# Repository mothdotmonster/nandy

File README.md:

# Nandy the NAND Gate

Nandy is a great friend who can help you make all kinds of decisions, as long as you decision has two digital inputs and one digital output.

Nandy is a breadboard-compatible NAND gate that you can hold in your hand. it's made as a teaching tool for electronics beginners to be able to learn how logic gates work with a simple and fun example of one.

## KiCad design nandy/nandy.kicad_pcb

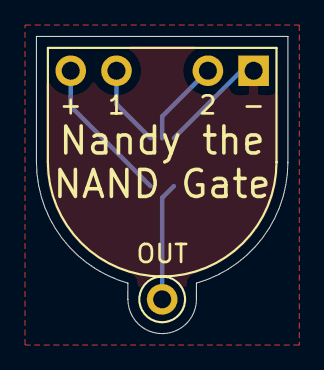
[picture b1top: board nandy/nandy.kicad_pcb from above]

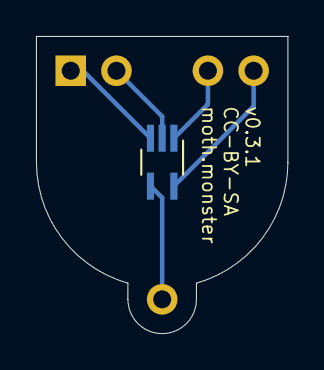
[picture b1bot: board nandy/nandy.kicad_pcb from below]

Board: 2 copper layers, 14.0 x 16.5 mm, 4 parts (4 on the bottom side), 5 nets.

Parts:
J1, J2: Conn_01x02_Male; PinHeader_1x02_P2.54mm_Vertical
J3: OUT; PinHeader_1x01_P2.54mm_Vertical
U1: 74LVC1G00; SOT-353_SC-70-5_Handsoldering

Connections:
/1: J1.1, U1.1
/2: J2.2, U1.2
/OUT: J3.1, U1.4
GND: J2.1, U1.3
VCC: J1.2, U1.5

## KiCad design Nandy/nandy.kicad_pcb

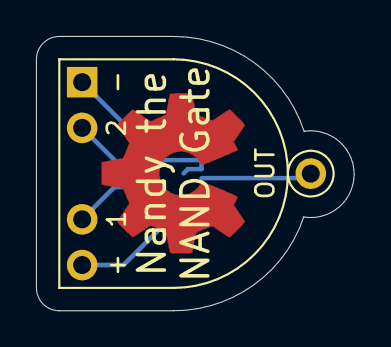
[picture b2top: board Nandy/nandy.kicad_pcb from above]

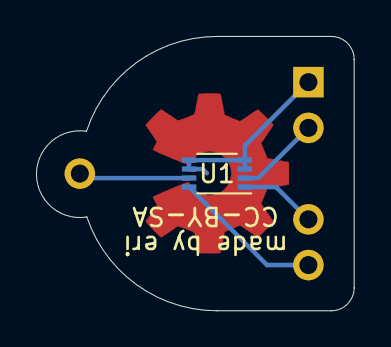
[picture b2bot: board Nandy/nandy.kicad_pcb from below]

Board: 2 copper layers, 17.7 x 15.2 mm, 4 parts (4 on the bottom side), 5 nets.

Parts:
J1, J2: Conn_01x02; PinHeader_1x02_P2.54mm_Vertical
J4: OUT; PinHeader_1x01_P2.54mm_Vertical
U1: 74LVC2G00; VSSOP-8_2.3x2mm_P0.5mm

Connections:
GND: J2.1, U1.3, U1.4, U1.5, U1.6
unnamed: J1.1, U1.1
unnamed: J2.2, U1.2
unnamed: J4.1, U1.7
VCC: J1.2, U1.8

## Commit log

2021-04-10 Add license
2021-04-10 Add gitignore
2021-04-10 Add the actual PCB
2021-04-10 Add first picture
2021-04-10 removing unessecary files
2021-04-16 add logo and website link
2021-04-28 total redesign

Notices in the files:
Nandy/nandy.kicad_pcb:
CC-BY-SA
